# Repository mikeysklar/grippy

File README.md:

# Grippy – Ultracompact One-Handed Keyboard

## Overview

Originally designed as a one-handed chording keyboard for wearables, Grippy has grown through five iterations into a slim, ultralight everyday-carry note-taking device.

Typing around 30 WPM with a single hand—and even inside your pocket—is completely realistic.

Grippy also doubles as a USB or BLE keyboard for phones, tablets, and computers.

---

## Features

- **Slim & Lightweight**
  - About the thickness of a AAA battery  
  - ~7× lighter than an iPhone  

- **One-Handed SAIE Chording**
  - Full text entry: letters, numbers, symbols  
  - Three layers, zero finger travel  

- **EDC Note-Taking**
  - Write and review notes directly on the device  
  - Works even while pocketed  

- **USB Keyboard Mode**
  - USB HID for quick input or macros  

- **BLE Keyboard Mode**
  - Wireless typing to phones and computers  

- **USB Storage Mode**
  - Mounts as a flash drive to edit notes  

- **Open & Hackable**
  - KiCad, STEP, FreeCAD, and 3MF files  
  - CircuitPython 10.x firmware + chording config

---

## Specs

| Item        | Value                  |
| ----------- | ---------------------- |
| Dimensions  | 61 x 35 x 11 mm        |
| Weight      | 29 grams               |
| Firmware    | CircuitPython 10.x     |
| Controller  | ESP32-S3               |
| Construction| SMD components on PCB  |

---

## PCB

- KiCAD 9.x
- single sided PCB
- SMT design

---

## Stencil

- low temp 140C solderpaste
- laser cut metal business card

---

## Schematic

---

## CircuitPython Setup

- <a href="https://circuitpython.org/board/espressif_esp32s3_devkitc_1_n8/">Bootloader 0.35.0 or later</a>
- <a href="https://circuitpython.org/board/espressif_esp32s3_devkitc_1_n8/">CircuitPython 10.0.3 or later</a>

install library dependencies:

```
circup install adafruit_st7789 adafruit_display_text adafruit_hid
```

copy code:

```
cp src/* CIRCUITPY/
```

---

## BOM

| Part                                                                                                  | Desc.                | Qty |
| ------------------------------------------------------------------------------------------------------ | -------------------- | --- |
| <a href="https://amzn.to/4idmH0o">ESP32-S3 SuperMini</a> | dual-core 240MHz / 512KB SRAM / 4MB Flash   | 1   |
| <a href="https://amzn.to/484M9jT">1.69” TFT Display</a> | ST7789 SPI           | 1   |
| <a href="https://www.digikey.com/en/products/detail/panasonic-electronic-components/EVQ-PUL02K/286340">Panasonic Tactile Switch</a> | EVQ-PUL02K SPST-NO Side Actuated | 1 |
| <a href=https://amzn.to/48axBAR>Standoff</a> | M2 × 5 mm | 4   |
| <a href=https://amzn.to/44vQJXr>Screws</a>| M2 × 5 mm            | 8   |
| <a href=https://www.aliexpress.us/item/3256804992051151.html>Female SMD Header</a> | 8-pin                | 1   |
| <a href=https://www.aliexpress.us/item/3256807383526945.html>Rt Ang Male Header | 8-pin                | 1   |
| <a href=https://www.ebay.com/itm/357161444108>Small LiPo Battery | 130 mAh (JST-1.25)   | 1   |
| <a href="https://www.aliexpress.us/item/3256805695475806.html">Slide Switch</a>| MSTK-12c03 | 1   |

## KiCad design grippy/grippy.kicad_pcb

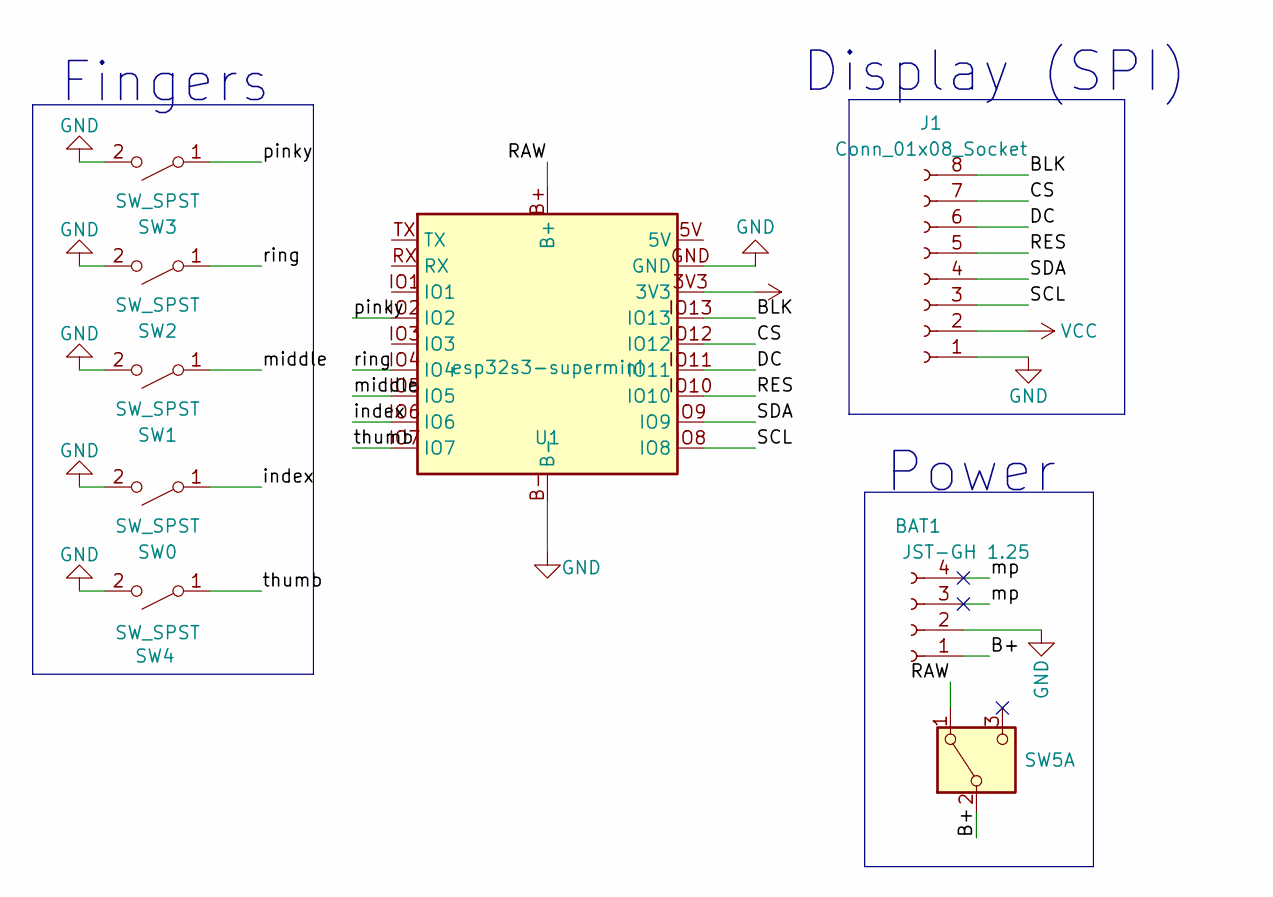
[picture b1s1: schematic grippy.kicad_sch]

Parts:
BAT1: JST-GH 1.25; JST_GH_SM02B-GHS-TB_1x02-1MP_P1.25mm_Horizontal
J1: Conn_01x08_Socket; tft-169-st7789
SW0, SW1, SW2, SW3, SW4: SW_SPST; Panasonic_EVQPUL_EVQPUC
SW5: SW_DPDT_x2; Untitled
U1: esp32s3-supermini; ESP32-S3-SuperMini_SMT

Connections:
/B+: BAT1.1, SW5.2 (B)
/BLK: J1.8, U1.IO13
/CS: J1.7, U1.IO12
/DC: J1.6, U1.IO11
/RAW: SW5.1 (A), U1.B+
/RES: J1.5, U1.IO10
/SCL: J1.3, U1.IO8
/SDA: J1.4, U1.IO9
/index: SW0.1 (A), U1.IO6
/middle: SW1.1 (A), U1.IO5
/mp: BAT1.3, BAT1.4
/pinky: SW3.1 (A), U1.IO2
/ring: SW2.1 (A), U1.IO4
/thumb: SW4.1 (A), U1.IO7
GND: BAT1.2, J1.1, SW0.2 (B), SW1.2 (B), SW2.2 (B), SW3.2 (B), SW4.2 (B), U1.B-, U1.GND
VCC: J1.2, U1.3V3

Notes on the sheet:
Fingers
Display (SPI)
Power

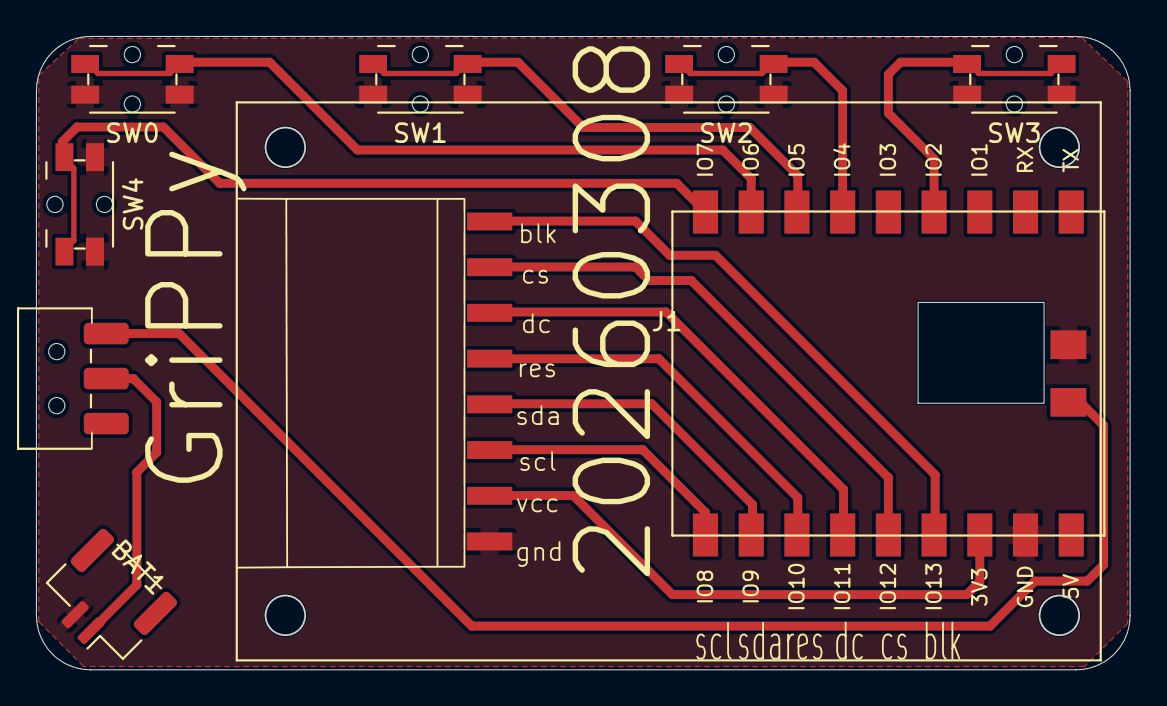
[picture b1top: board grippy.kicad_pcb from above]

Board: 2 copper layers, 60.8 x 35.2 mm, 9 parts (0 on the bottom side), 16 nets.

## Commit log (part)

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2025-09-03 got some pcb and tft going
2025-09-03 got a board
    ready to burn
2025-09-04 milled, stencil
2025-09-06 got a fairly usable case
2025-09-06 case looks tight
    really slammed the key inserts right up against the mechanical buttons
2025-09-08 display running + chords
    quickly changed over to ST7789 got chords going. adding addition lines for more chars.
2025-09-08 13 col x 5 row
    65 chars per screen full.
2025-09-12 bumped the size up
2025-09-12 height adjustment on case
2025-09-12 new stl
2025-09-14 design changes
    having a working unit, still needs refinemine for speed
2025-09-14 faster spi bump
2025-09-14 little faster auto_refresh off
2025-09-14 bigger fonts helps
    chords are being enterered faster.
    8 x 3 layout = 24 chars feels right for now.
2025-09-14 non-blocking scans
2025-09-14 tighten up fixed vars
2025-09-14 faster
    shrunk chord timers.
2025-09-15 40 chars per screen
    adjusted terminalio for 10 chars per line and 4 lines. Using magenta now. Looks pretty good.
2025-09-16 profiler
    Code feel 5x faster with separate labels for each line.
2025-09-16 removed profiling
    runs smoothly
2025-09-16 profile removed
    all time.sleep() pulled form check_chords. Runs well.
2025-09-24 new design
    shorter, thicker with big fat pink buttons. plenty of room for a 150mA battery.
2025-09-25 fabbed / printed
    untested, but the physical fit and layout look good.
2025-09-27 kicad mods
    * raised display height to 8mm
    * slide thumb button
    * changed tft header location 1.25mm slide toward mcu
    * rotated power plug
2025-10-01 working model
2025-10-01 push test
2025-10-01 cap pwrswitch cutout, thumb holder, .6 mechchanical switch size
2025-10-01 changed mechanical button gap to 0.8mm, ideal
2025-10-10 display wait for come up
    every other power on was preventing the display from coming up.
2025-10-18 added new rt angle display connector
2025-10-19 new rt ang pcb stable started case
2025-10-20 finished adaptation to rt ang
    now buttons will fit on rt angle dropped display which has a 5mm gap / standoffs
2025-11-16 repo cleanup / readme started / images
2025-11-16 case
2025-11-16 bang
2025-11-16 table fix
2025-11-16 table out
2025-11-17 minor changes
2025-11-20 docs / BOM
2025-11-25 BOM updates
2025-12-02 added countersinks to top screws
2025-12-03 general updates
    ready to cut another pcb
2025-12-03 finish docs outoline
2025-12-03 fix code block
2025-12-03 renamed code.py
2025-12-03 dropped the old flatchord name
2025-12-10 one liners
2025-12-17 cut-out for new supermini
2026-02-04 moved battery receptacle
2026-02-04 thumb support
2026-03-08 switch to .2mm trace space
2026-03-08 wider
2026-05-26 display with full heaers
